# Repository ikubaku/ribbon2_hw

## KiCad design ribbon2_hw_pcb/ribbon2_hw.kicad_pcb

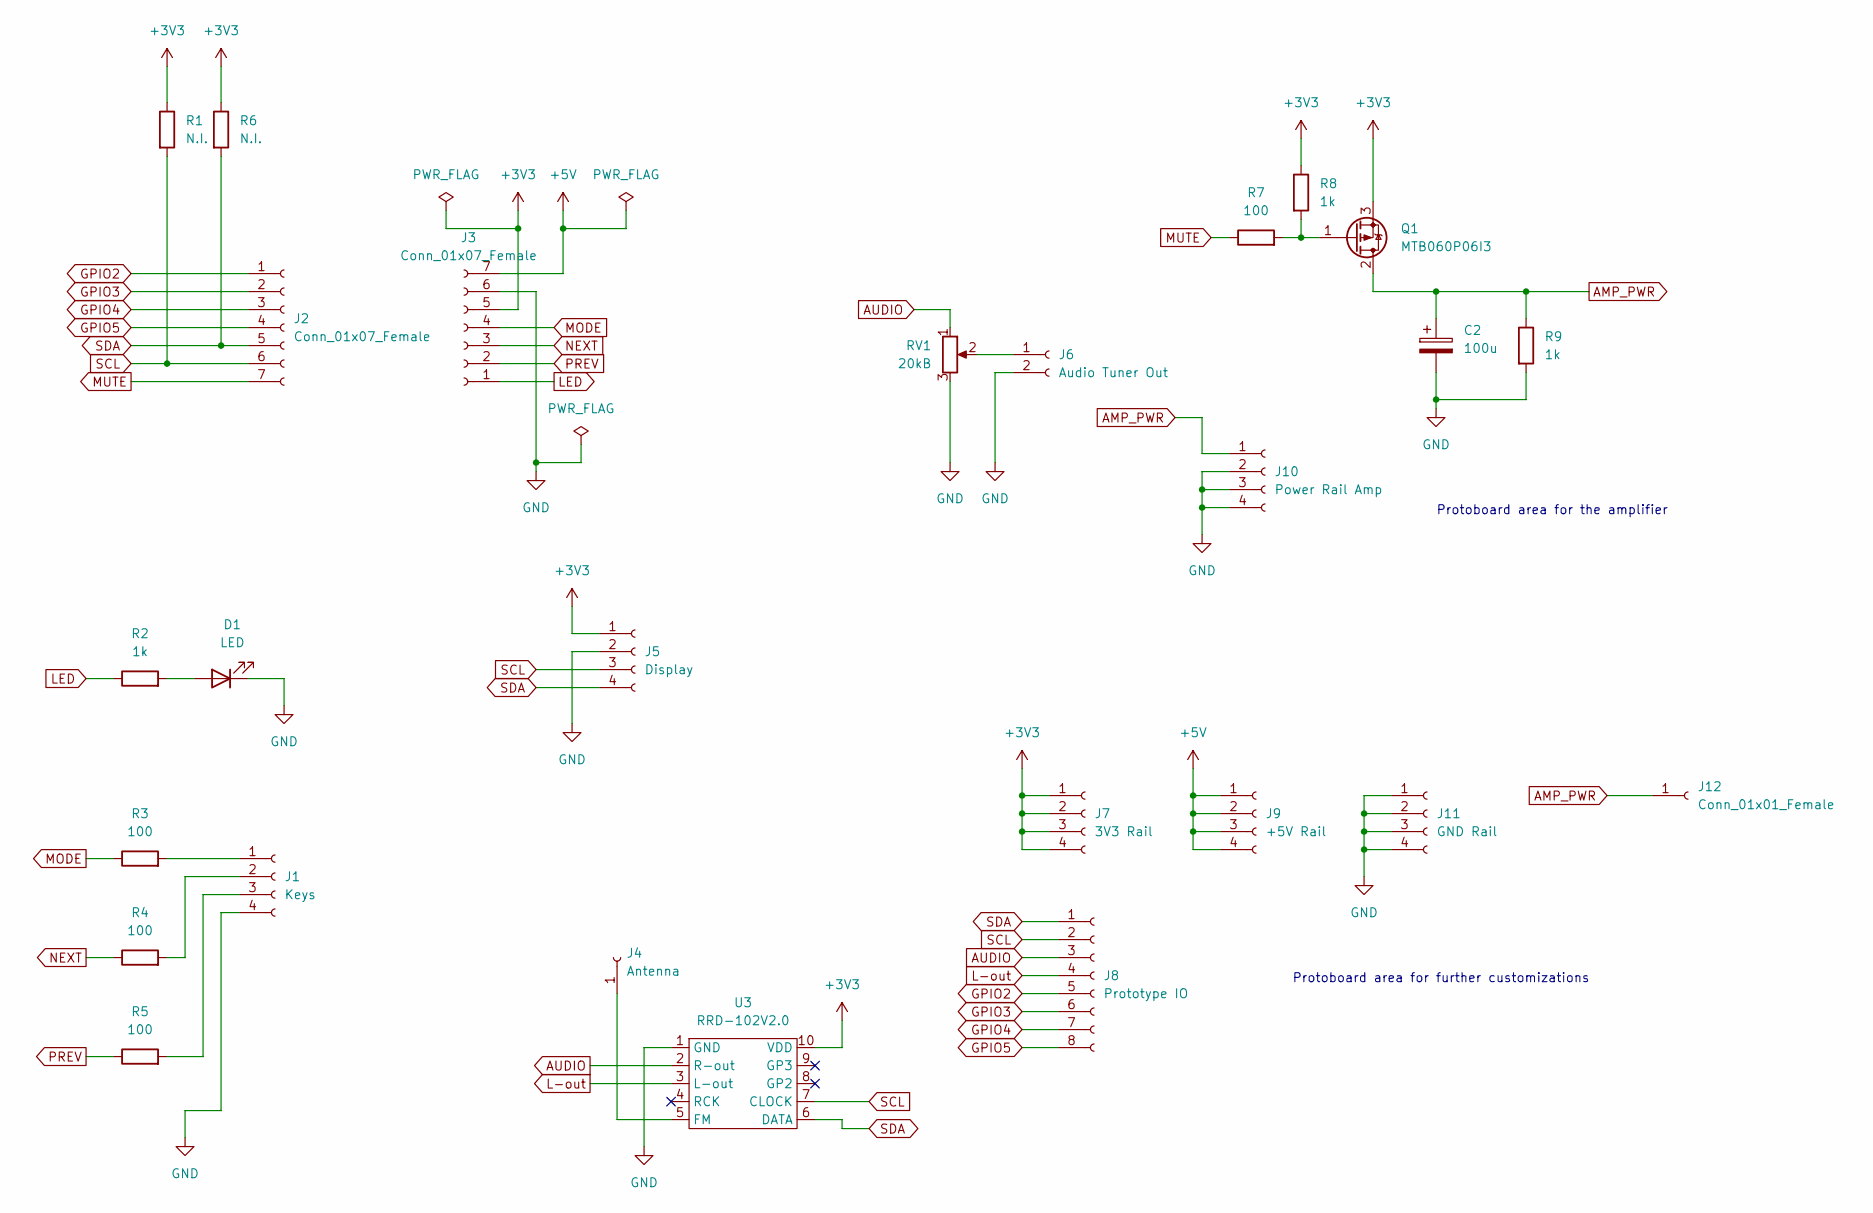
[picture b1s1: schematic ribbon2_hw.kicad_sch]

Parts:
C2: 100u; CP_Radial_D5.0mm_P2.00mm
D1: LED; LED_D3.0mm
J1: Keys; PinSocket_1x04_P2.54mm_Vertical
J2, J3: Conn_01x07_Female; PinSocket_1x07_P2.54mm_Vertical
J4: Antenna; PinSocket_1x01_P2.54mm_Vertical
J5: Display; PinSocket_1x04_P2.54mm_Vertical
J6: Audio Tuner Out; PinSocket_1x02_P2.54mm_Vertical
J7: 3V3 Rail; PinSocket_1x04_P2.54mm_Vertical
J8: Prototype IO; PinSocket_1x08_P2.54mm_Vertical
J9: +5V Rail; PinSocket_1x04_P2.54mm_Vertical
J10: Power Rail Amp; PinSocket_1x04_P2.54mm_Vertical
J11: GND Rail; PinSocket_1x04_P2.54mm_Vertical
J12: Conn_01x01_Female; PinSocket_1x01_P2.54mm_Vertical
Q1: MTB060P06I3; TO-251-3_Vertical
R1, R6: N.I.; R_Axial_DIN0207_L6.3mm_D2.5mm_P10.16mm_Horizontal
R2, R8, R9: 1k; R_Axial_DIN0207_L6.3mm_D2.5mm_P10.16mm_Horizontal
R3, R4, R5, R7: 100; R_Axial_DIN0207_L6.3mm_D2.5mm_P10.16mm_Horizontal
RV1: 20kB; TSR-3386K
U3: RRD-102V2.0; RRD-102v2.0

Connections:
+3V3: J3.5, J5.1, J7.1, J7.2, J7.3, J7.4, Q1.3 (S), R1.1, R6.1, R8.1, U3.10 (VDD)
+5V: J3.7, J9.1, J9.2, J9.3, J9.4
AMP_PWR: C2.1, J10.1, J12.1, Q1.2 (D), R9.1
AUDIO: J8.3, RV1.1, U3.2 (R-out)
GND: C2.2, D1.1 (K), J1.4, J3.6, J5.2, J6.2, J10.2, J10.3, J10.4, J11.1, J11.2, J11.3, J11.4, R9.2, RV1.3, U3.1 (GND)
GPIO2: J2.1, J8.5
GPIO3: J2.2, J8.6
GPIO4: J2.3, J8.7
GPIO5: J2.4, J8.8
L-out: J8.4, U3.3 (L-out)
LED: J3.1, R2.1
MODE: J3.4, R3.1
MUTE: J2.7, R7.1
NEXT: J3.3, R4.1
unnamed: D1.2 (A), R2.2
unnamed: Q1.1 (G), R7.2, R8.2
unnamed: J1.1, R3.2
unnamed: J1.2, R4.2
unnamed: J1.3, R5.2
unnamed: J6.1, RV1.2
unnamed: J4.1, U3.5 (FM)
PREV: J3.2, R5.1
SCL: J2.6, J5.3, J8.2, R1.2, U3.7 (CLOCK)
SDA: J2.5, J5.4, J8.1, R6.2, U3.6 (DATA)

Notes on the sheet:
Protoboard area for the amplifier
Protoboard area for further customizations

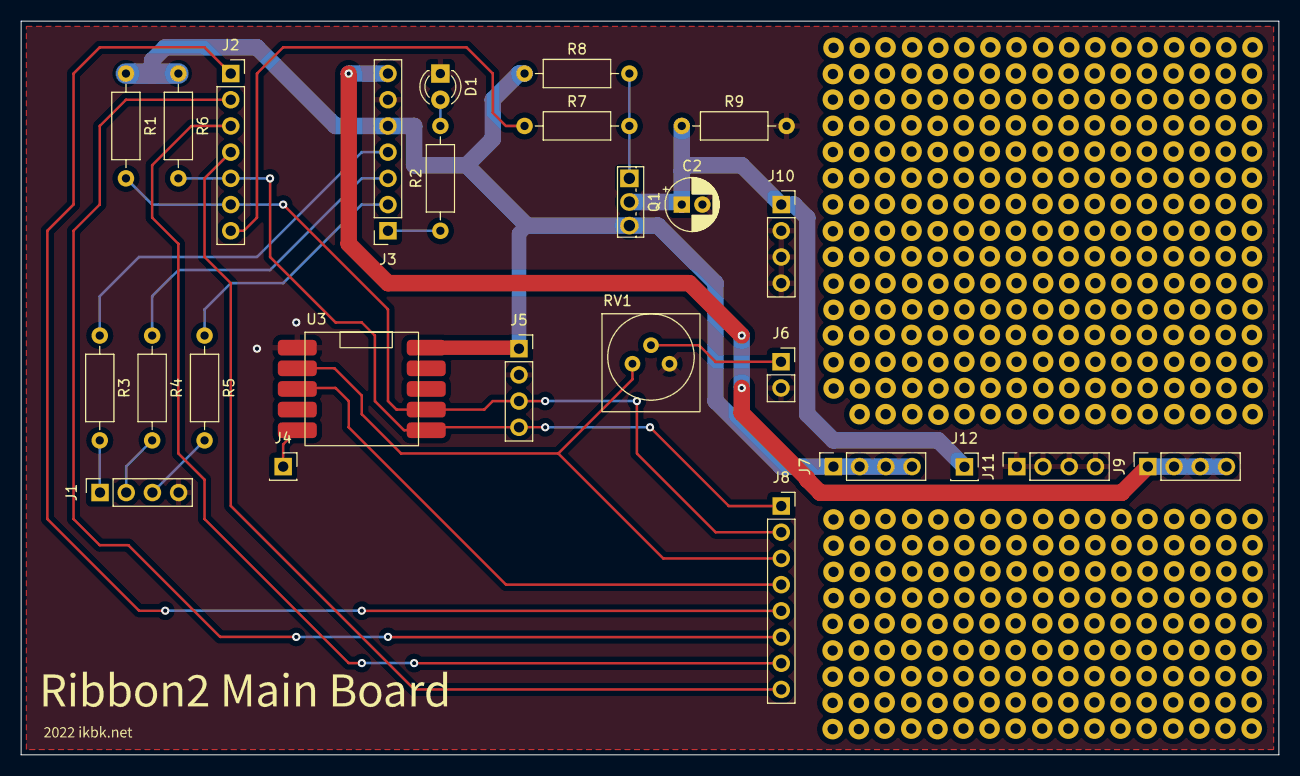
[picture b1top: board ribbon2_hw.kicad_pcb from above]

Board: 2 copper layers, 121.9 x 71.1 mm, 26 parts (0 on the bottom side), 24 nets.

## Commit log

2022-11-27 Add files
